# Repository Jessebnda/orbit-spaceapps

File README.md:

# ORBIT: Onboard Risk & Behavioral Insight Tracker

<p align="center"><b>🏆 Local winner · NASA Space Apps Challenge 2026, Mexicali</b></p>

**NASA Space Apps Challenge 2026** · Challenge: *Create Health Monitoring Software for Astronauts on Space Missions* · CETYS Universidad, Mexicali

ORBIT is a wearable and software system that lets a crew watch its own physical and behavioral health **with no link to Earth**. Sensor garments stream vitals to each astronaut's wrist phone. The phone sends them over the habitat's local network to a mission computer, which runs the rules, raises emergencies, prescribes protocols and answers the commander through an AI assistant that runs entirely on board.

**▶ Demo video (30 s):** [docs/media/orbit-demo.mp4](docs/media/orbit-demo.mp4)

**Quick links:** [Demo video](docs/media/orbit-demo.mp4) · [Technical paper (ES, .md)](docs/ORBIT-paper.md) · [Paper (.docx)](docs/ORBIT-paper.docx) · [Features](#features) · [On-board AI](#on-board-ai-a-92-gb-model-on-a-24-gb-laptop) · [NASA data](#nasa-data-and-resources) · [Hardware and CAD](#hardware-and-cad) · [Firmware](firmware) · [Run it](#run-it) · [Status and limits](#status-and-limits)

> 📄 **Read the technical paper:** [ORBIT paper](docs/ORBIT-paper.md) ([.docx](docs/ORBIT-paper.docx)), written in Spanish, the team's language. It covers the challenge, the two-layer architecture, the hardware design, three use cases (routine monitoring, risk prediction and SOS) and its references. This README is the full English version of the project.

## High-level summary

ORBIT is a health monitor that a crew wears and runs on board, with no link to Earth. A smart vest, a wrist band and a head camera stream vitals to each astronaut's wrist phone. The phone turns those readings into a simple daily picture, and a companion pet named Orbi turns healthy habits into a game. A laptop on board collects the whole crew's data, raises emergencies and prescribes protocols, and it gives the commander an AI assistant that answers from NASA research. It addresses the challenge because the crew can catch a slow decline in heart health, sleep, exercise or mood themselves, before it becomes an emergency, even when Earth is minutes away.

## The problem

On Moon and Mars missions the crew faces radiation, isolation, confinement and altered gravity, while messages to Earth take minutes and the crew are not doctors. Health checks still depend mostly on ground teams and scattered data. NASA's Human Research Program names isolation and confinement and distance from Earth among the five hazards of spaceflight, and behavioral risk grows with mission length.

## A day with ORBIT

1. **Morning.** The astronaut puts on the vest and the wrist band. The chest light glows in the colour of their pet and the phone on the wrist shows *Today*: heart rate, blood oxygen, pressure and temperature against their normal range, plus a one-minute check-in on mood, stress and how the mission feels.
2. **Daily tests.** The app asks for a short physical test (5 jumps in place, counted by the vest's motion sensor) and a reaction game. Results go to the crew's achievements and leaderboard, so exercise becomes a shared game instead of a chore.
3. **During work.** The astronaut turns the phone sideways and gets ship mode: big readable vitals, the next task and a hold-to-SOS button. The vest light pulses with each heartbeat and turns red as heart rate rises, so crewmates can see stress at a glance.
4. **Feeling low.** Orbi, the companion pet, gets hungry, wants company and notices low mood, short sleep or high stress. The astronaut can talk to it; it runs on the phone, so it works offline, and its advice is drawn from NASA behavioral-health guidance.
5. **The commander's view.** On the mission laptop the commander sees every crew member live, who is out of range, who is near whom (Bluetooth proximity between phones, so isolation inside the crew is visible), and can send a protocol to anyone. Asking the assistant "Who is out of range right now?" returns an answer built from live data and NASA sources, with its reasoning shown as it thinks.
6. **Emergency.** If an astronaut holds SOS, or the hub sees critical vitals, every screen goes red with an alarm. The nearest crewmates are shown first, and the phone walks them through CPR adapted for microgravity, step by step.

## What we built

| Part | What it does | Where |
|---|---|---|
| **Wearables** | ESP32 chest vest (ECG at 250 Hz, heart rate, motion, skin temperature, LED light), wrist band (heart rate, motion), head band (ESP32 camera on the forehead that takes photos hands-free while the phone is busy in ship mode, worn in the team photo) | [`firmware/`](firmware), 3D-printed enclosures designed for microgravity in [`hardware/`](hardware) |
| **Crew app** | Today, check-in, daily tests, Orbi the companion pet, achievements, leaderboard and explorations, crew album, ship mode, SOS with CPR guide | [`mobile/`](mobile) (Expo, iOS, Android and web) |
| **Mission hub** | Validates every reading, applies thresholds, detects emergencies, logs check-ins, tracks news from home and prescribes protocols per astronaut | [`hub/`](hub) (Node, runs on the commander's laptop) |
| **Commander dashboard** | Live crew board, per-astronaut detail and trends, proximity map, protocols, crew album, AI assistant with NASA sources | [`dashboard/`](dashboard) (Next.js) |
| **Shared contract** | One set of types, thresholds, messages and texts used by all parts, with self-checks | [`shared/`](shared) |

## Hardware and CAD

We designed and 3D printed our own enclosures in SolidWorks (by Erick Blanco Nakashima). Every part is in [`hardware/`](hardware) as printable STL and editable STEP, plus a full assembly in `.glb` that GitHub opens as an interactive 3D view.

| Device | Inside | CAD |
|---|---|---|
| **Chest vest** | ESP32, ECG front end (250 Hz), MPU6050 motion sensor, GY-906 skin temperature, WS2812 LED ring behind a translucent logo disc | [3D view](hardware/vest/PecheraAssem.glb) · [STL](hardware/vest/stl) · [STEP](hardware/vest/step) |
| **Wrist band** | XIAO ESP32-C3 with MPU motion sensor in its own box, rail sled and phone mount | [3D view](hardware/wrist/MunecaAssem.glb) · [STL](hardware/wrist/stl) |
| **Head band** | ESP32 with a camera on the forehead: hands-free photos while the phone is in ship mode, sent over Bluetooth to the crew album | firmware in [`firmware/`](firmware) |
| **Wrist phone** | Android phone that runs the crew app and a local AI model | mount: `soporte_S23plus_v3_respaldo_plano.STL` |

**Custom PCB (by Alejandro Pineda Aguirre).** A sensor board designed in KiCad that replaces loose wiring: sockets for the ESP32, a MAX30102 heart rate and blood oxygen sensor and an MPU6050 motion sensor, a screw terminal for power and the ORBIT logo on the silkscreen. KiCad project: [schematic](hardware/vest/kicad%20pecho.kicad_sch) · [board](hardware/vest/kicad%20pecho.kicad_pcb).

**Bill of materials (approximate retail prices, USD, per astronaut):**

| Part | Qty | Approx. cost |
|---|---|---|
| ESP32 dev board (vest) | 1 | $6 |
| ECG front end (AD8232-type) with leads and electrodes | 1 | $15 |
| MPU6050 motion sensor (vest and wrist) | 2 | $6 |
| GY-906 infrared skin temperature sensor | 1 | $12 |
| WS2812 LED ring | 1 | $5 |
| MAX30102 heart rate and SpO2 sensor | 1 | $4 |
| Custom PCB (small batch, per board) | 1 | $2 |
| XIAO ESP32-C3 (wrist band and head band) | 2 | $10 |
| Camera module (head band) | 1 | $8 |
| Batteries, regulators, wiring | set | $15 |
| PLA for printed enclosures (about 250 g) | | $5 |
| Straps, elastic band, screws | set | $10 |
| **Wearables total** | | **≈ $98** |
| Android phone (any phone able to run a 4B model; we used ones we already had) | 1 | existing |
| Mission laptop (one per crew) | 1 | existing |

The wearables cost under $100 per person with off-the-shelf parts, so the system is cheap to replicate for analog missions, research stations or classrooms.

**Links between devices.** Each link uses the protocol that fits its data:

| Link | Protocol | Why |
|---|---|---|
| Vest → phone | Bluetooth Classic (serial profile) | Continuous 250 Hz ECG plus motion needs a steady, high-rate stream; the phone sends the pet colour back for the LED ring |
| Wrist band → phone | Bluetooth Low Energy | Small, periodic heart rate and motion packets; low power for a battery band |
| Head band → phone | Bluetooth Low Energy | The phone asks for a photo with one command; the JPEG comes back in chunks sized to the BLE packet (up to 244 bytes) |
| Phone ↔ phone | Bluetooth Low Energy scanning | Signal strength (RSSI) between crew phones is turned into approximate distance for proximity and nearest-responder SOS |
| Phone ↔ mission laptop | Wi-Fi, WebSocket on the habitat's local network | All crew data, protocols, SOS and photos; no internet needed |
| Planned | ESP-NOW body network with LoRa repeaters | Longer range across the whole habitat |

**Why a phone on the wrist and not a smartwatch:** a watch cannot run a language model on board. A phone has the memory to run the companion's AI fully offline, a screen big enough for ship mode, Bluetooth to every sensor and Wi-Fi to the mission laptop. Design notes for spaceflight materials are in [`hardware/README.md`](hardware/README.md#design-for-spaceflight).

## Features

ORBIT treats health as physical and psychological at once. NASA's research says isolation, monotony and distance wear a crew down slowly, so most features are built around three ideas from psychology: **feeling seen** (someone notices how you are), **belonging** (you are part of a crew, not alone in a can), and **motivation through progress** (small, visible wins that make healthy habits stick).

### 1. Know how you are: Today, check-in and insights

- **Today screen.** Heart rate, blood oxygen, blood pressure and temperature, each against its normal range, plus daily goals for activity, food and water with a mark for where you should be by now.
- **Daily check-in (one minute).** Mood (an interactive shape that changes with your answer), stress (calm to very high), mission outlook (pessimistic to optimistic), plus free text for discomfort and a note. NASA's isolation studies use the same kind of short daily self-report to catch mood drift early.
- **Insights.** After 5 days the app compares your last 3 days with the days before and tells you in plain words when something changed, with a 7-day chart: sleep down an hour or more, mood falling, talking to the crew less than half as much, gaming much more while mood drops, or patterns such as "your mood follows your sleep" and "your stress drops on active days".

### 2. Motivation through progress: achievements, levels and leaderboard

Long missions are monotonous, and exercise is a countermeasure astronauts must keep up for months. ORBIT makes progress visible:

- **10 achievements with XP**, for example *First log* (first check-in), *Stable orbit* (7-day check-in streak), *Countermeasure* (120 minutes of exercise in a day), *Circadian* (3 nights of 7 hours or more), *Long walk* (10 km in total) and *Lifesaver* (a CPR drill).
- **Levels.** Every 500 XP is a new level, shown as a ring on your profile that fills as you go.
- **Crew leaderboard.** Ranks the day's *effort points*: minutes of activity, checking in, time spent with the pet and distance explored, capped so nobody wins by overtraining. It rewards taking care of yourself, not raw performance.

### 3. Explorations: a Strava for the crew

- Log each outing or training session (an EVA walk, a treadmill run, a habitat circuit) with a title, place, stopwatch time and distance. The app works out the pace.
- Each outing appears in the crew feed on the dashboard with its route card, pace and a **personal record** badge when it is someone's longest, plus weekly totals and a crew ranking by kilometres.
- Like Strava, the point is social: seeing crewmates' outings and cheering for records builds the shared routine that NASA's team research links to cohesion.
- *Prototype note:* distance is typed in and the route drawing is illustrative; GPS-free indoor tracking from the vest's motion sensor is the next step.

### 4. Never alone: Orbi, the companion pet

- Every astronaut has **Orbi**, a small creature on the wrist. You pick one of 5 shapes and 6 suit colours, and **the vest's chest light glows in that same colour**, so your pet is literally on you.
- Orbi has three needs: **food**, **affection** and **company**. They empty over hours (8, 6 and 12) and you refill them by feeding, petting and talking to it. Caring for something small every day is a gentle routine with a reason behind it.
- Orbi reads your state. It gets **sad** if your last check-in showed low mood or high stress and you have not talked since, if a vital is critical, or if a need runs out; it gets **tired** when you slept under 6 hours. Its face is a mirror that nudges you to check in.
- **Talk to Orbi.** A chat with an AI that runs on the phone, so it works with no network. Suggested openers ("I want to tell you how my day is going", "I feel tired") lower the barrier to talking. If a message sounds like a crisis, Orbi always answers with a fixed line that points to a human crewmate.
- **Guided session (4 minutes).** How do you feel, two short questions, three breathing cycles, close.

### 5. Belonging: proximity, team contact and news from home

- **Who is near whom.** Every phone listens for the other crew phones over Bluetooth and turns signal strength into approximate distance. The commander sees a live map of the crew.
- **Isolation alerts.** The hub keeps minutes of contact per person and channel (voice, text, in person) and compares the last 24 hours with a 7-day baseline. It flags **withdrawal** (less than half the usual contact), a **spike** (2.5 times the usual), and a **dropped peer** (someone you talked to on most days but not today). Withdrawal or a dropped peer sends a *Talk to a crewmate* protocol.
- **News from home.** When the commander learns of hard news for a crew member (a loss in the family, for example), they log it once. That person stays on *watch* for 14 days, receives a grief support protocol, and the commander is reminded too. Bad news far from home is one of the situations NASA's behavioral guidance singles out.
- **Crew album.** The head-band camera (an ESP32 with a camera, worn on the forehead) takes photos hands-free, so the astronaut can capture evidence or a moment while the wrist phone is busy sideways in ship mode. Photos go straight into a shared album on every phone and on the dashboard. Shared moments are part of feeling like a crew.

### 6. Daily care: protocols and tests

- **Protocol library:** emergency (CPR in microgravity, hypoxia, fever, hypertensive crisis, panic attack), physical (jumping exercise, hydration, sleep hygiene, eat a full meal) and mental (box breathing, talk to a crewmate, grief support, 5-minute journal). Each one is a short list of steps on the phone.
- **Who sends them.** The hub's rules (for example low activity late in the day, under 6 hours of sleep, low water, low mood or high stress, hard news, isolation alerts), the commander by hand, or the AI assistant. Each protocol is sent at most once every 30 minutes, so nobody gets nagged.
- **Daily tests.** A physical test of **5 jumps in place**, counted by the vest's motion sensor (heart rate is ignored during the test because motion distorts it), and a **5-try reaction test** for alertness. A **CPR drill** keeps rescue skills fresh.
- **Orbit Defender.** A short arcade game (waves of enemies, coins, shields and extra lives) for a break, which also counts toward an achievement and toward the insights on gaming versus mood.

### 7. Emergencies

- **Automatic triggers** from the vitals: heart rate under 30 or over 180 (or under 40 with oxygen under 85%), blood oxygen under 88%, temperature of 39 °C or more, or blood pressure of 180/120 or more.
- **Manual SOS:** hold the red button on the wrist.
- **The nearest two crewmates are called first**, using the same Bluetooth distance; if nobody is in range, everyone online is alerted.
- The person in trouble sees a calm message; rescuers see that they are first or second responder, and for cardiac arrest the phone runs a **CPR guide for microgravity** (110 compressions per minute, 30:2, switch rescuers every 2 minutes). The dashboard shows a red banner, a timer, responders with their distance and an alarm sound; resolving takes a deliberate two-step confirmation.

### 8. The commander's dashboard

- Crew overview with status (normal, watch, critical), averages for sleep and activity, and live cards with each person's vitals.
- Detail per astronaut: every metric against its range and a 7-day average, heart rate charts over 6 hours, 24 hours or 14 days, check-ins, contact history and news from home.
- Proximity map, explorations feed, leaderboard, protocols (send one or write a new one), crew album, and the AI assistant described below.

### 9. Ship mode and the chest light

- **Ship mode.** Turn the wrist phone sideways and it becomes a glanceable HUD: big vitals, the next task, sensor links and the SOS button, readable while working.
- **Chest light.** The vest's LED ring shows the pet's colour, pulses with each heartbeat and blends to red as heart rate climbs from 100 to 130 bpm, so crewmates can see stress without asking.

| Today | Companion pet | Pet chat |
|---|---|---|
|  |  |  |

**Ship mode.** Turn the wrist phone sideways and the app becomes a glanceable HUD: vitals in range, the next task, sensor links and a hold-to-SOS button.

**Commander dashboard.** The whole crew at a glance, and protocols the commander can send to any crew member.

<sub>Screenshots show the interface translated to English; the app currently ships in Spanish, the team's language. Vitals in screenshots come from the crew simulator.</sub>

### How it works

```
 Vest ESP32 ─ Bluetooth Classic (250 Hz ECG + IMU) ─┐
 Band ESP32 ─ BLE ──────────────────────────────────┼─► Crew phone (wrist) ── WebSocket on the habitat LAN ──► Mission hub
 Head ESP32 ─ BLE (camera) ─────────────────────────┘     on-device LLM pet                                  rules · emergencies · RAG · agent
                                                                                                                │
                                                                                     Commander dashboard ◄──────┤
                                                                                     local LLM (llama.cpp) ◄────┘
```

- **No internet needed.** Every model runs on board: a small model on the phone and a 92 GB model on the mission laptop (see below).
- **Store and forward.** If the network drops, the phone queues up to 500 messages and sends them when it reconnects.
- **Emergencies both ways.** The astronaut can trigger SOS from the wrist, or the hub raises one from the vitals. The dashboard and every phone show it, and the phone walks the crew through CPR adapted for microgravity.
- **Behavioral health, not just vitals.** Daily check-ins, reaction tests, team interaction (proximity between crew phones) and news from home feed the risk picture, following NASA's Human Research Program behavioral risk.

### On-board AI: a 92 GB model on a 24 GB laptop

A crew far from Earth cannot call a cloud model, and medical data should never leave the ship. So the commander's assistant runs a large model entirely on the mission laptop (a MacBook Pro M5 Pro with 24 GB of RAM).

**The model.** Qwen3.8 Flash Next, a mixture-of-experts (MoE) model, quantized to IQ4_XS: about 92 GB on disk, roughly four times the laptop's memory. Each token only activates a few experts, so the whole model never needs to be in RAM at once. The model was used **only locally**: open weights downloaded once and run on our own laptop, with no API, no account and no data sent anywhere.

**The llama.cpp fork.** We serve it with a fork of llama.cpp ([npanj/llama.cpp](https://github.com/npanj/llama.cpp)) that adds expert streaming (`--moe-stream`):

| Piece | Setting | Why |
|---|---|---|
| Expert streaming | `--moe-stream --moe-stream-direct` | Experts are read from the SSD on demand instead of loading the full 92 GB |
| Expert cache | `--moe-stream-cache 9` (9 GB), 8 I/O threads, look-ahead prefetch | Hot experts stay in RAM; the next ones are fetched while the current token computes |
| KV cache | `-ctk q8_0 -ctv q8_0`, flash attention, 16k context | Long conversations fit next to everything else |
| GPU | `-ngl 99` (Apple Metal) | All dense layers on the GPU |
| Sleep | `--sleep-idle-seconds 300` | The model unloads after 5 minutes idle (about 12 to 15 GB active, near zero asleep) and wakes on the next question |

The launch script is [`hub/scripts/llm.sh`](hub/scripts/llm.sh). It serves an OpenAI-compatible API on `localhost:8080` with no network access and no computer-control tools. Generation runs at about 9 tokens per second, so the hub streams the model's thinking to the dashboard as it arrives instead of leaving the commander staring at a spinner.

**Tools.** The assistant ([`hub/src/services/agent.ts`](hub/src/services/agent.ts)) is a tool-calling agent. Each question runs up to 4 rounds: the model thinks, calls tools, reads the results and answers; the last round has no tools, so it must answer with what it gathered. Its eight tools:

| Tool | What it does |
|---|---|
| `get_crew_overview` | Live vitals, status and last contact for every crew member |
| `get_member_history` | One astronaut's trends over time |
| `get_comms` | Minutes of conversation today and isolation anomalies against the member's own baseline |
| `get_behavior_insights` | 7-day behavior analysis: sleep, mood, communication and jump tests |
| `search_knowledge` | Retrieval over the NASA knowledge base (below) |
| `list_protocols` | The protocol library |
| `trigger_protocol` | Sends a protocol to an astronaut's phone, with a reason |
| `create_protocol` | Writes a new protocol (mental, physical or emergency) and sends it |

Every tool call and its result are shown under the answer, so the commander can check what the model actually looked at.

**Retrieval (RAG).** The NASA documents in [`hub/kb/`](hub/kb) are split into ~800-character chunks with overlap ([`hub/src/services/rag.ts`](hub/src/services/rag.ts)), embedded with `multilingual-e5-small` (about 120 MB, runs in Node through transformers.js) and stored in PostgreSQL with pgvector. A question is embedded the same way and the closest chunks come back with their source, which the model cites. If the database is down, the hub keeps the same index in memory and ranks by cosine similarity, so retrieval still works. Run `npm run ingest` in `hub/` after adding a document.

**On the phone.** The companion pet uses a separate 1-bit Bonsai-4B model (about 570 MB) through llama.rn, so it works with no network at all and is released from memory after 2 minutes idle.

More detail: [Technical paper (Spanish)](docs/ORBIT-paper.md) ([.docx](docs/ORBIT-paper.docx)) · [Architecture](docs/ARCHITECTURE.md) · [Conventions](docs/CONVENTIONS.md) · [Design brief](docs/product/DESIGN-BRIEF.md)

## From NASA research to features

Isolation and confinement and distance from Earth are two of the five hazards named by NASA's Human Research Program (HRP), and the chance of an adverse behavioral event grows with mission length. Each ORBIT feature answers one of these findings:

| NASA finding (paraphrased) | ORBIT feature | Source |
|---|---|---|
| Isolation and confinement weigh most on behavioral health on long missions; distance, microgravity and radiation add to it | The whole app is organized around the crew's mental state, not only vitals | HRP 5 Hazards; [`hub/kb/salud-conductual-nasa.md`](hub/kb/salud-conductual-nasa.md) |
| Positive mood drifts down with time in isolation and tracks operational performance | Daily check-in (mood, stress, mission outlook) tracked as a trend; a gradual dip is not an alarm by itself | APEX results (NTRS 20260002661); [`apex-resultados.md`](hub/kb/apex-resultados.md) |
| Small stressors accumulate into worst-case scenarios, so small trends are worth watching | Companion pet "Orbi" notices low mood, high stress or short sleep and gives short supportive cards | Picano and Holland 2024 (NTRS 20240000994) |
| Sleep loss degrades attention, reaction time and emotional regulation | Sleep feeds the pet's guidance; the reaction game and protocols give a quick performance check | [`sueno-en-mision.md`](hub/kb/sueno-en-mision.md) |
| Crew friction tends to grow over a mission | Bluetooth proximity between crew phones shows who is near whom, so isolation inside the crew is visible and the nearest crewmates answer an SOS first | NASA team-risk evidence report 2022; [`trabajo-en-equipo-nasa.md`](hub/kb/trabajo-en-equipo-nasa.md) |
| Bad news from home hits hard, and grief at a distance has its own needs | "News from home" watch: the commander logs it, the crew member stays on watch for 14 days and the pet switches to supportive, honest cards | [`duelo-a-distancia.md`](hub/kb/duelo-a-distancia.md); WHO psychological first aid |
| Behavioral risk is low on 6-month missions but rises with duration and distance | An on-board assistant for the commander that works with no link to Earth; SOS and CPR flows for acute events | HRP evidence report 2025; [`riesgo-conductual-nasa.md`](hub/kb/riesgo-conductual-nasa.md) |

**How:** the commander's on-board assistant retrieves these documents (retrieval over [`hub/kb/`](hub/kb) through its `search_knowledge` tool) and cites each one's NASA source. The phone's small model has no retrieval, so the same evidence is distilled into the pet's tips ([`shared/src/petTips.ts`](shared/src/petTips.ts)).

## NASA data and resources

The knowledge base ([`hub/kb/`](hub/kb)) is built from these sources (paraphrased, each file cites its source):

- NASA Human Research Program, *Human Research Program hazards* (isolation and confinement, sleep, distance from Earth): https://www.nasa.gov/hrp/hazards/
- NASA HRP Evidence Report, *Risk of Adverse Cognitive or Behavioral Conditions and Psychiatric Disorders* (2025): https://ntrs.nasa.gov/citations/20250001454
- NASA OCHMO-TB-016, *Behavioral Health and Performance*, Rev B (2023): https://www.nasa.gov/wp-content/uploads/2023/12/ochmo-tb-016-behavioral-health.pdf
- NASA HRP Evidence Report, *Risk of Performance and Behavioral Health Decrements Due to Inadequate Cooperation, Coordination, Communication, and Psychosocial Adaptation within a Team* (2022): https://ntrs.nasa.gov/citations/20220007465
- Picano and Holland, *Behavioral Health and Performance*, NASA CLDP MedOps Workshop (2024): https://ntrs.nasa.gov/citations/20240000994
- Bell et al., *Summary Results from the APEX Standardized Suite*, NASA HRP Investigators' Workshop (2026): https://ntrs.nasa.gov/citations/20260002661 and https://ntrs.nasa.gov/citations/20250011721

Space agency partner and other sources:

- ESA / DGLRM guideline for CPR in microgravity (2020): https://pmc.ncbi.nlm.nih.gov/articles/PMC7607644/
- WHO, *Psychological first aid: Guide for field workers* (2011): https://www.who.int/publications/i/item/9789241548205

## Benefits and goals

- **Autonomy.** The crew watches its own health on board; Earth becomes a backup, not the bottleneck.
- **Early warning.** Trends in vitals, sleep, mood and team contact show a decline days before it becomes an emergency.
- **Adherence.** The pet, achievements and leaderboard make check-ins and exercise something the crew wants to do.
- **Faster response.** SOS reaches every screen at once, and CPR steps are on the wrist when seconds count.
- **On Earth too.** The same kit fits isolated teams such as Antarctic stations, submarines, offshore rigs and remote clinics.

Next we want to align thresholds with NASA-STD-3001, move the body network to ESP-NOW with LoRa repeaters across the habitat, add a radiation dose sensor, and test ORBIT in a space analog habitat.

## Beyond space

Nothing in ORBIT is tied to our vest. The hub accepts vitals from any source, so data exported from an Apple Watch, a Fitbit or any other wearable could feed the same rules, protocols and assistant. And because the assistant answers from NASA's research on isolation, confinement and behavioral health, which applies to anyone who lives far from help, the same system works wherever people are isolated and offline:

- Antarctic and Arctic research stations, submarines, offshore platforms and remote mines
- Expeditions, ships at sea and military deployments
- Rural clinics and communities without reliable internet
- Older adults who live alone, and their families or caregivers
- Remote and night-shift workers

Everything runs on a phone and a laptop with no internet, so it could be deployed in any of these places tomorrow.

## Tools

TypeScript across the stack · React Native with Expo (iOS, Android, web) · Next.js and Tailwind (dashboard) · Node with WebSockets (hub) · PostgreSQL with pgvector, optional Supabase · llama.cpp fork with MoE expert streaming and Qwen3.8 Flash Next (on-board AI), transformers.js embeddings, llama.rn with Bonsai-4B on the phone · ESP32 and XIAO ESP32-C3 with Arduino (ECG module, MPU6050, GY-906, WS2812 LEDs) · SolidWorks enclosures (STL and STEP), 3D printed in PLA.

## Run it

### Requirements

- Node.js 20 or newer and npm (the repo is an npm workspace: `shared`, `hub`, `dashboard`, `mobile`)
- Docker, optional, for the local pgvector database (`docker-compose.yml`); without it the hub keeps the knowledge index in memory
- For the on-board assistant: the [npanj/llama.cpp](https://github.com/npanj/llama.cpp) fork built with Metal, an open-weight GGUF model, and `LLAMA_SERVER` / `ORBIT_MODEL` set as in [`.env.example`](.env.example)
- For the crew app on a phone: Expo (Android or iOS); the web build runs in any browser
- For the wearables: `arduino-cli` with the ESP32 core

Copy `.env.example` to `.env`, then `npm install` at the root.

```bash
npm run db         # local pgvector (Docker); optional, the hub falls back to memory
npm run hub        # mission hub on :8790
npm run sim        # 4 simulated crew members (add -- --emergency c2)
npm run dashboard  # commander dashboard
npm run mobile     # crew app (Expo)
npm run check      # contract self-checks
```

The assistant needs a llama.cpp server on `:8080` (`LLM_URL`). Firmware builds with `arduino-cli` for `esp32:esp32:esp32` (vest) and the XIAO ESP32-C3 (wrist band and head band).

## Repository structure

```
orbit-spaceapps/
├── shared/      types, thresholds, messages and texts used by every part, with self-checks
├── hub/         mission hub (Node): rules, emergencies, protocols, RAG, AI agent
│   ├── kb/          NASA knowledge base (paraphrased, each file cites its source)
│   └── scripts/     llm.sh (on-board model), sim.ts (crew simulator), ingest
├── dashboard/   commander dashboard (Next.js)
├── mobile/      crew app (Expo: Android, iOS, web)
├── firmware/    ESP32 vest, wrist band and head band sketches
├── hardware/    3D-printed enclosures: STL, STEP and GLB assemblies
├── supabase/    database schema (pgvector)
├── brand/       logo and lockup
└── docs/        technical paper, architecture, conventions, media
```

## Privacy and ethics

- **Data never leaves the habitat.** Vitals, check-ins and photos stay on the phones and the mission laptop. Every AI model runs locally; nothing is sent to a cloud service.
- **The astronaut sees their own data first.** The phone shows each person their vitals, trends and insights; the commander sees crew status to keep everyone safe, which is how flight surgeons and crew already work.
- **Mood is self-reported.** ORBIT does not guess emotions from a camera or microphone. The check-in is a short, voluntary self-report, as in NASA's isolation studies.
- **The head-band camera only takes photos when the wearer asks**, and they go to a crew album everyone can see.
- **No gamified vital signs.** Achievements reward habits (exercise, sleep, check-ins), never "good" blood pressure or oxygen, so nobody is pushed to hide symptoms.
- **AI supports, it does not diagnose.** The assistant shows which data and NASA sources it used, and a crisis message from an astronaut is always answered by pointing to a human crewmate.

## Status and limits

- **Working:** vest streaming 250 Hz ECG, heart rate, IMU and skin temperature to the phone over Bluetooth, chest LED light painted in the astronaut's pet colour that pulses with each heartbeat and turns red as heart rate rises, crew app on iOS, Android and web, hub, dashboard, on-board assistant with NASA sources, SOS flow, daily protocols.
- **Enclosures** are PLA prototypes. A flight version would use flame-retardant, low off-gassing materials such as ULTEM 9085 or PEEK ([details](hardware/README.md#design-for-spaceflight)).
- **Not measured by wearables:** glucose, EEG, bone and muscle loss. The hub prescribes a check on the ship's dedicated equipment instead.
- **Thresholds** are generic adult clinical ranges for now (`shared/src/index.ts`), and emergency triggers are in `hub/src/domain/rules.ts`; the next step is to align them with NASA-STD-3001.
- **Planned:** ESP-NOW body network with LoRa repeaters across the habitat, a radiation dose sensor, and a 3D crew status view.

## Use of AI

- **In the product:** a 1-bit Bonsai-4B model runs on the phone for the companion pet. Qwen3.8 Flash Next, served by a llama.cpp fork, powers the commander's assistant, which uses retrieval over the NASA knowledge base and tools to read crew data.
- **In development:** the team used an AI coding assistant (Claude Code) to help write and review code across the repository. The idea, the hardware and all design decisions are the team's own. No AI-generated images or NASA branding are used.

## Acknowledgements

NASA Space Apps Challenge and the Mexicali local event organizers; CETYS Universidad; NASA's Human Research Program and the open NTRS archive, whose research forms the knowledge base; and the open-source projects listed under Tools.

## Team

Jorge Humberto Ibarra Flores · Alejandro Pineda Aguirre · Francisco Javier Castillo Osobampo · Erick Blanco Nakashima · Jesse Banda Chaidez

CETYS Universidad, Mexicali, Baja California, Mexico.

## License

[MIT](LICENSE)

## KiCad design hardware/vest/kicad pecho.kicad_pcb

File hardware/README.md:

# Hardware: mechanical designs

3D-printable parts for the ORBIT wearables. The electronics that go inside them are programmed from [`firmware/`](../firmware).

```
hardware/
├── wrist/
│   ├── MunecaAssem.glb    full wrist assembly (3D preview)
│   └── stl/               printable parts
└── vest/
    ├── PecheraAssem.glb   full chest vest assembly (3D preview)
    ├── step/              editable CAD (STEP)
    └── stl/               printable parts
```

- **`stl/`**: the files to slice and print.
- **`step/`**: neutral CAD files to open and edit in any CAD tool (SolidWorks, Fusion, FreeCAD, Onshape).
- **`.glb`**: the whole assembly in one file. GitHub shows it as an interactive 3D view, and it can be loaded in a web app with three.js.

## Design for spaceflight

ORBIT has to work on a crew that floats, works with its hands full and has no doctor on board. The enclosures were shaped around that:

- **Nothing floats away.** In microgravity anything you let go of drifts off and becomes a hazard in the cabin. The crew phone is fixed to the wrist, the sensor boxes are fixed to the body, and the vest covers are screwed shut, so no part comes loose during exercise or work.
- **One-handed, quick-release phone.** The phone mount slides onto the wrist band on a quick-release rail sled. An astronaut can take the phone off or put it back with one hand while the other holds a handrail. With the phone on the wrist, the SOS button is always within reach.
- **Sensors where the signal is.** The vest core sits over the chest so the ECG electrodes and heart-rate sensor stay close to the heart for a clean 250 Hz signal. The wrist box keeps the IMU tight against the forearm to measure movement and the daily physical test.
- **Health you can see from across the module.** The vest logo is a status light: a translucent disc diffuses the LED, a dark mask shapes it into the logo, and it pulses with each heartbeat in the astronaut's pet colour, turning red as heart rate rises. Crewmates can tell how someone is doing at a glance, without looking at a screen. This supports the team-awareness side of behavioral health, not only the vitals.
- **Protected electronics.** The armour cover closes over the vest core so bumps against walls and equipment in a tight habitat don't reach the boards.

**Prototype vs. flight version.** These parts are printed in PLA for the prototype. PLA is not acceptable in a spacecraft cabin. A flight version would be printed in flame-retardant, low off-gassing materials such as ULTEM 9085 or PEEK, and would have to pass NASA's flammability and off-gassing tests (NASA-STD-6001).

## Wrist (`wrist/`)

| File | Part |
|---|---|
| `wristleBand_v3.STL` | Wrist band |
| `soporte_S23plus_v3_respaldo_plano.STL` | Phone mount for the Samsung S23+ (flat back) |
| `trineo_rieles_v7b.stl` | Rail sled that holds the phone mount on the band |
| `caja_c3_mpu.stl` | Box for the XIAO ESP32-C3 and the MPU IMU |
| `caja_c3_mpu_tapa.stl` | Lid for the C3 + MPU box |

## Chest vest (`vest/`)

| Part | STL | STEP |
|---|---|---|
| Base that sits on the chest | `pechera_base.STL` | `pechera_base.step` |
| Core that holds the ESP32 and sensors | `pechera_nucleo.STL` | `pechera_nucleo.step` |
| Armour cover | `pechera_tapa_armadura.STL` | `pechera_tapa_armadura.step` |
| Logo cover over the LED status light | `pechera_logo_tapa.STL` | `pechera_logo_tapa.step` |
| Translucent logo disc (light diffuser) | | `pechera_logo_disco_translucido.step` |
| Dark logo mask | | `pechera_logo_mascara_oscura.step` |

Units are millimetres, as exported from SolidWorks.

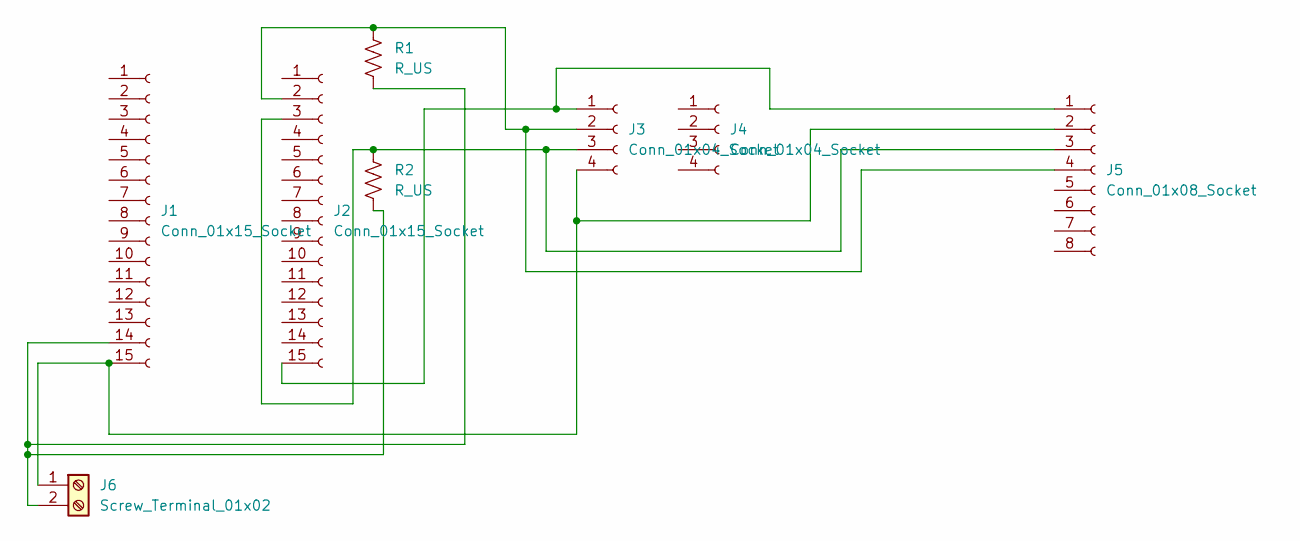
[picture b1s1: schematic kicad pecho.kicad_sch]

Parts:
J1, J2: Conn_01x15_Socket; PinSocket_1x15_P2.54mm_Vertical
J3, J4: Conn_01x04_Socket; PinSocket_1x04_P2.54mm_Vertical
J5: Conn_01x08_Socket; PinSocket_1x08_P2.54mm_Vertical
J6: Screw_Terminal_01x02; TerminalBlock_MaiXu_MX126-5.0-02P_1x02_P5.00mm
R1, R2: R_US; R_Axial_DIN0207_L6.3mm_D2.5mm_P10.16mm_Horizontal

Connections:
unnamed: J1.14, J6.2, R1.2, R2.2
unnamed: J1.15, J3.4, J5.2, J6.1
unnamed: J2.2, J3.2, J5.4, R1.1
unnamed: J2.3, J3.3, J5.3, R2.1
unnamed: J2.15, J3.1, J5.1

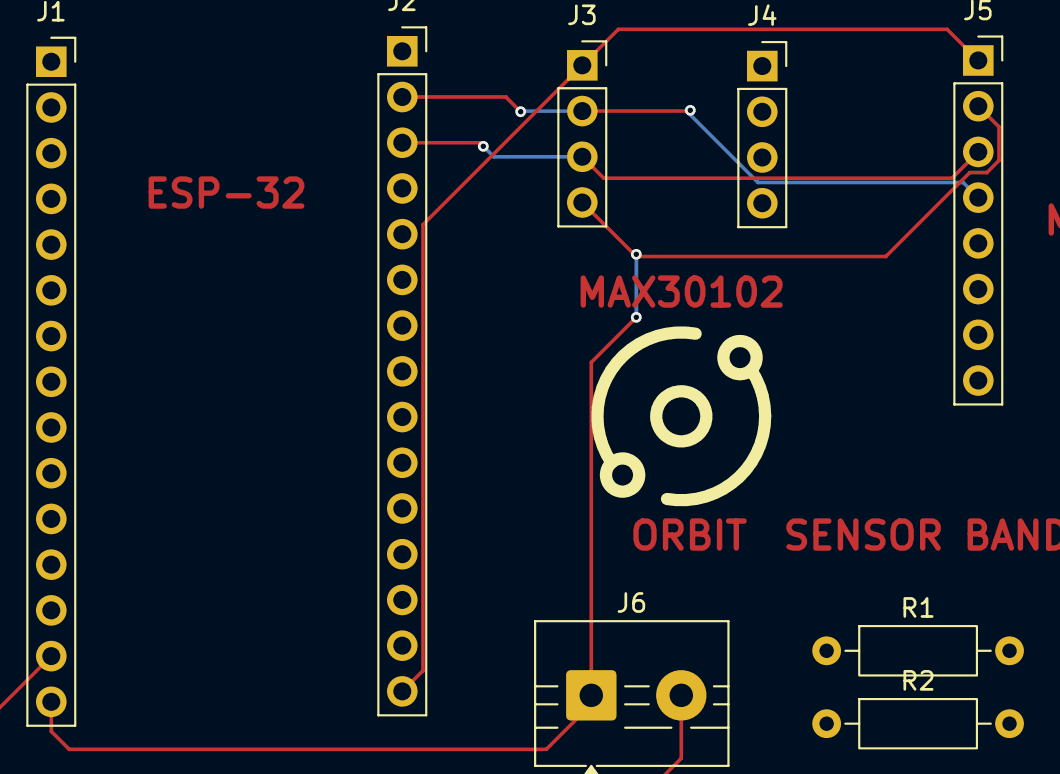
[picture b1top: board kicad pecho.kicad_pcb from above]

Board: 2 copper layers, 8 parts (0 on the bottom side), 5 nets.
